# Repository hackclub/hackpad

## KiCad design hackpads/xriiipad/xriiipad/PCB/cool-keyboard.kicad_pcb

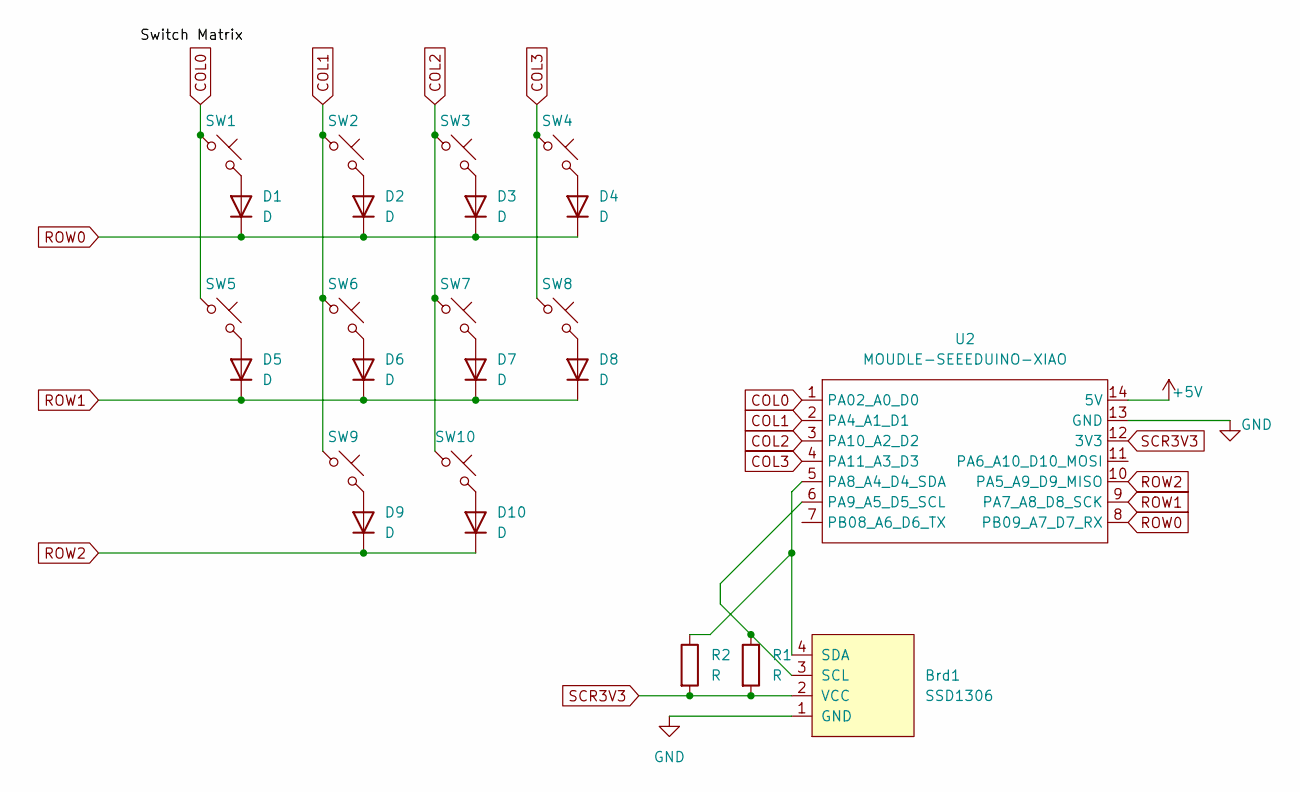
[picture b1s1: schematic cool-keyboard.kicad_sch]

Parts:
Brd1: SSD1306; 128x64OLED
D1, D2, D3, D4, D5, D6, D7, D8, D9, D10: D; D_A-405_P10.16mm_Horizontal
R1, R2: R; R_Axial_DIN0204_L3.6mm_D1.6mm_P5.08mm_Horizontal
SW1, SW2, SW3, SW4, SW5, SW6, SW7, SW8, SW9, SW10: SW_Push_45deg; MX-Solderable-1U
U2: MOUDLE-SEEEDUINO-XIAO; MOUDLE14P-2.54-21X17.8MM

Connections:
+5V: U2.14 (5V)
COL0: SW1.1, SW5.1, U2.1 (PA02_A0_D0)
COL1: SW2.1, SW6.1, SW9.1, U2.2 (PA4_A1_D1)
COL2: SW3.1, SW7.1, SW10.1, U2.3 (PA10_A2_D2)
COL3: SW4.1, SW8.1, U2.4 (PA11_A3_D3)
GND: Brd1.1 (GND), U2.13 (GND)
unnamed: Brd1.3 (SCL), R1.1, U2.6 (PA9_A5_D5_SCL)
unnamed: Brd1.4 (SDA), R2.1, U2.5 (PA8_A4_D4_SDA)
unnamed: D1.2 (A), SW1.2
unnamed: D2.2 (A), SW2.2
unnamed: D3.2 (A), SW3.2
unnamed: D4.2 (A), SW4.2
unnamed: D5.2 (A), SW5.2
unnamed: D6.2 (A), SW6.2
unnamed: D7.2 (A), SW7.2
unnamed: D8.2 (A), SW8.2
unnamed: D9.2 (A), SW9.2
unnamed: D10.2 (A), SW10.2
ROW0: D1.1 (K), D2.1 (K), D3.1 (K), D4.1 (K), U2.8 (PB09_A7_D7_RX)
ROW1: D5.1 (K), D6.1 (K), D7.1 (K), D8.1 (K), U2.9 (PA7_A8_D8_SCK)
ROW2: D9.1 (K), D10.1 (K), U2.10 (PA5_A9_D9_MISO)
SCR3V3: Brd1.2 (VCC), R1.2, R2.2, U2.12 (3V3)

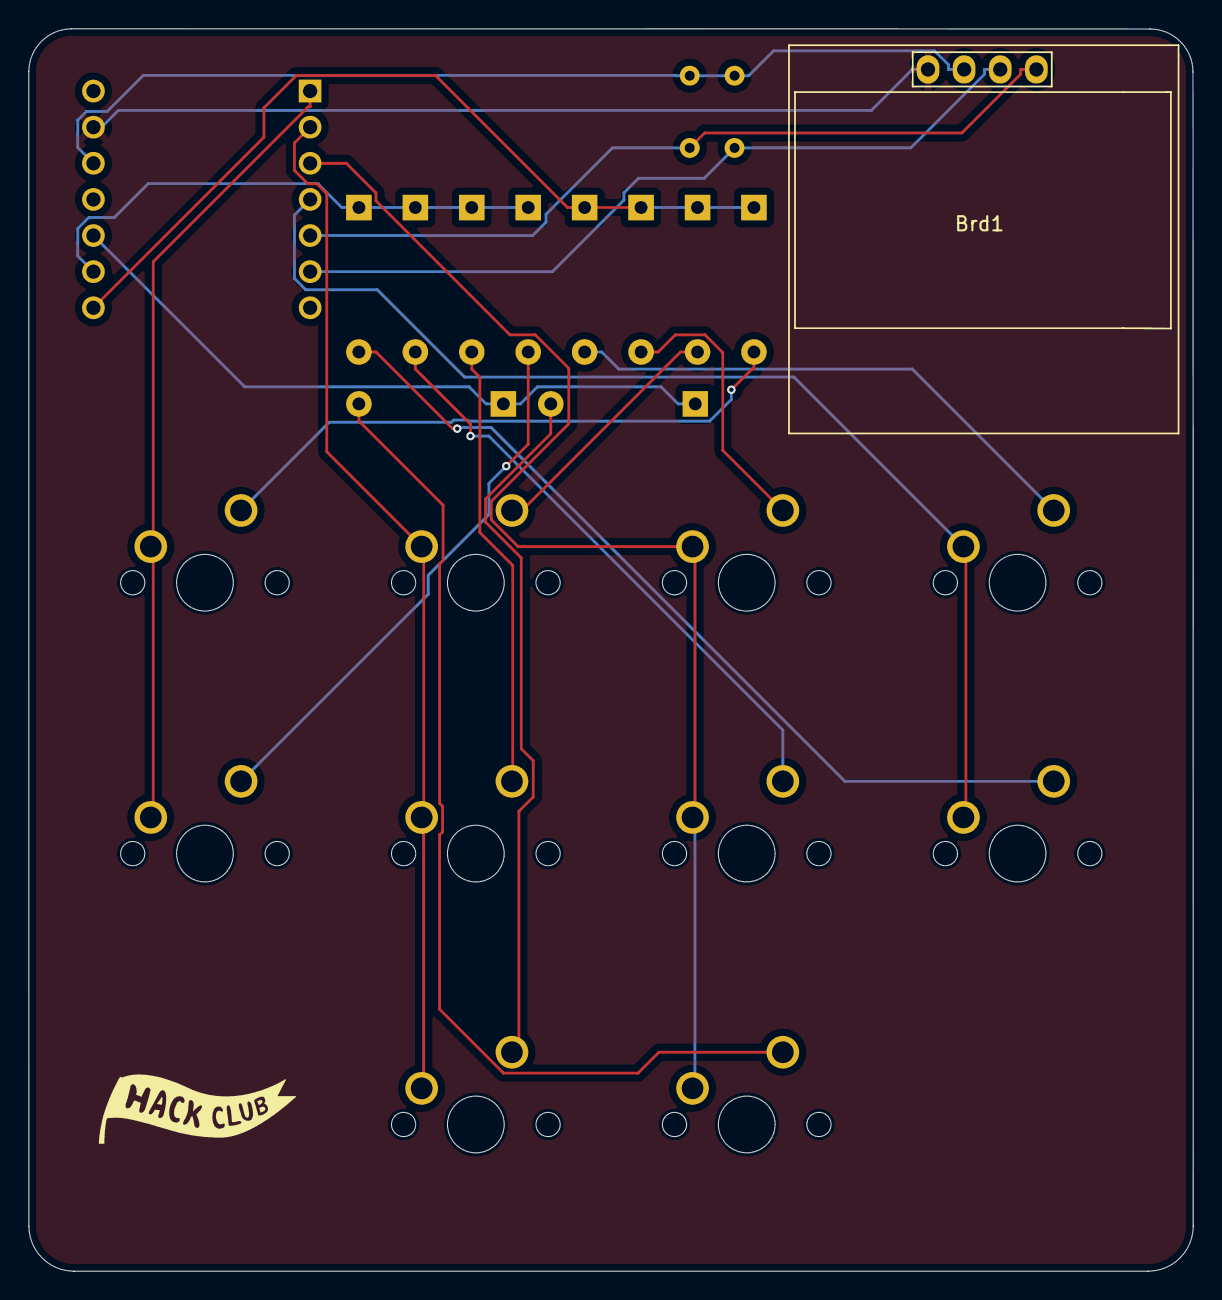
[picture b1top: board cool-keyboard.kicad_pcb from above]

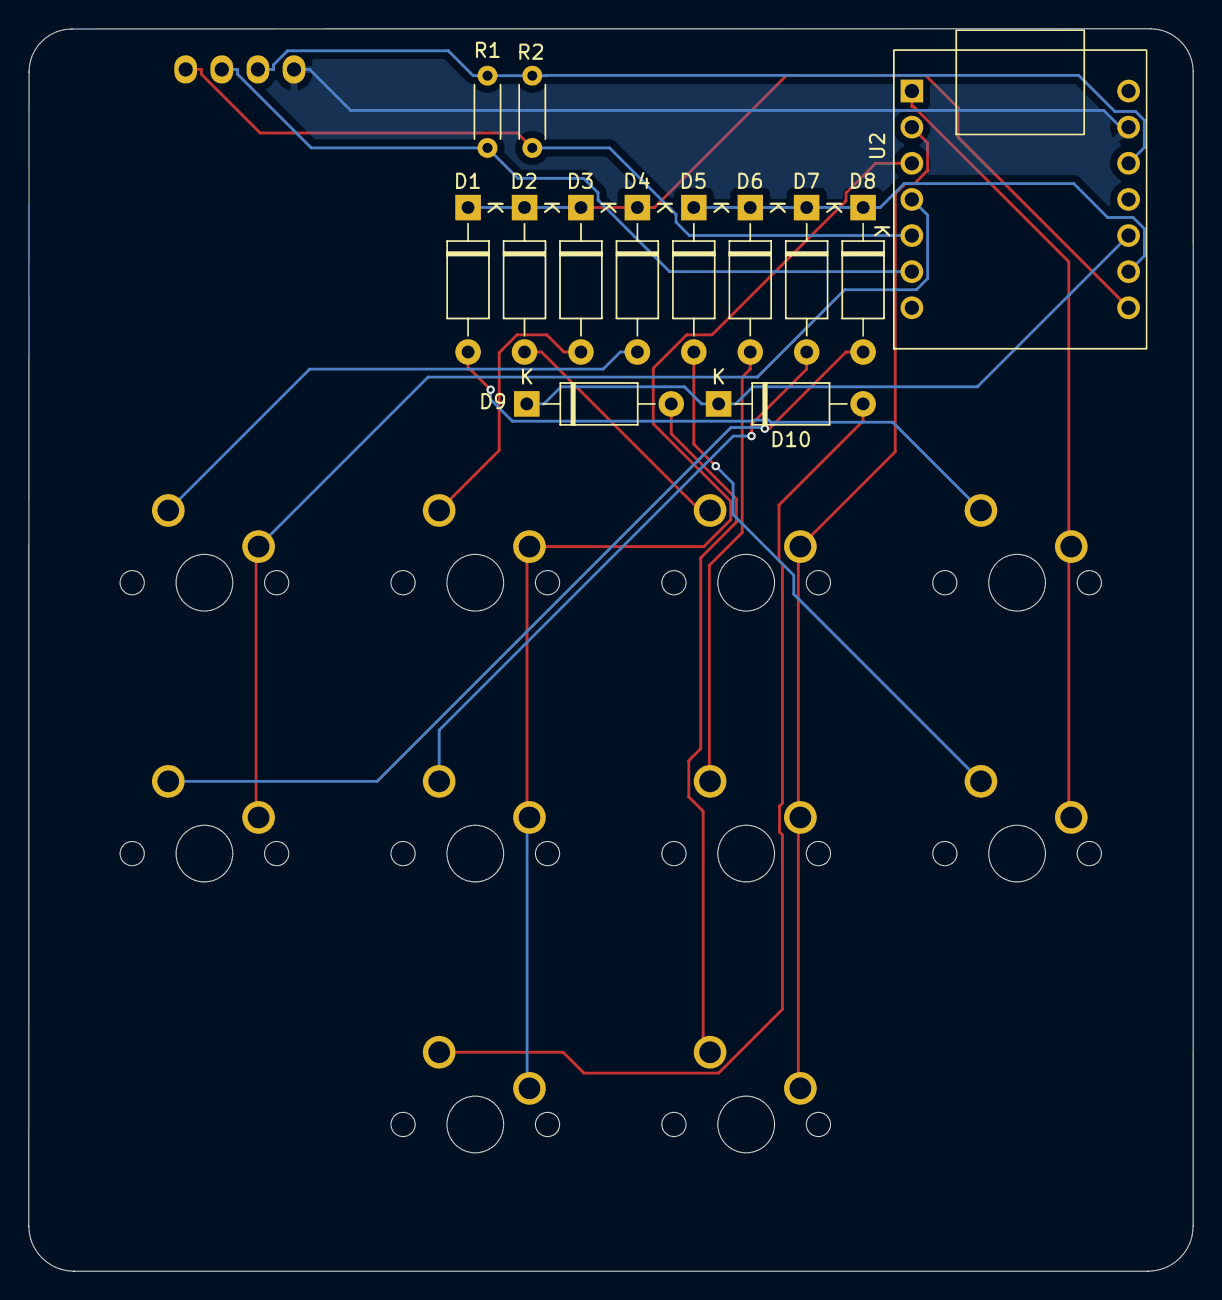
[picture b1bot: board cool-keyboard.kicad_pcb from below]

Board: 2 copper layers, 81.9 x 87.4 mm, 24 parts (13 on the bottom side), 21 nets.

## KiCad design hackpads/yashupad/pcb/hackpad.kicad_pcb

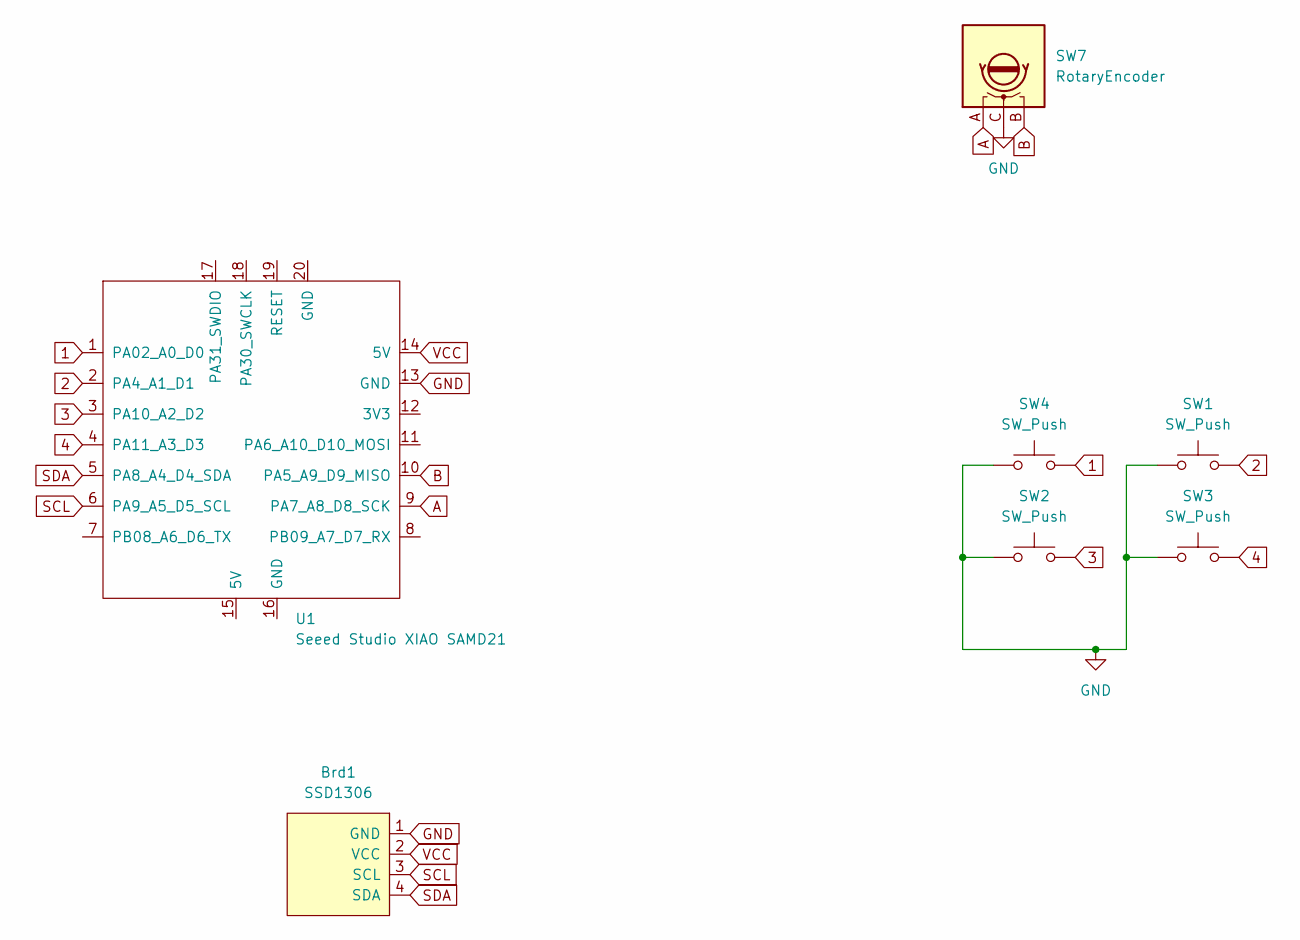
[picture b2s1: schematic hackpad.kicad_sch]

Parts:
Brd1: SSD1306; 128x64OLED
SW1, SW2, SW3, SW4: SW_Push; SW_Cherry_MX_1.00u_PCB
SW7: RotaryEncoder; RotaryEncoder_Alps_EC11E-Switch_Vertical_H20mm
U1: Seeed Studio XIAO SAMD21; XIAO-Generic-Thruhole-14P-2.54-21X17.8MM

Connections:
1: SW4.2, U1.1 (PA02_A0_D0)
2: SW1.2, U1.2 (PA4_A1_D1)
3: SW2.2, U1.3 (PA10_A2_D2)
4: SW3.2, U1.4 (PA11_A3_D3)
A: SW7.A, U1.9 (PA7_A8_D8_SCK)
B: SW7.B, U1.10 (PA5_A9_D9_MISO)
GND: Brd1.1 (GND), SW1.1, SW2.1, SW3.1, SW4.1, SW7.C, U1.13 (GND)
SCL: Brd1.3 (SCL), U1.6 (PA9_A5_D5_SCL)
SDA: Brd1.4 (SDA), U1.5 (PA8_A4_D4_SDA)
VCC: Brd1.2 (VCC), U1.14 (5V)

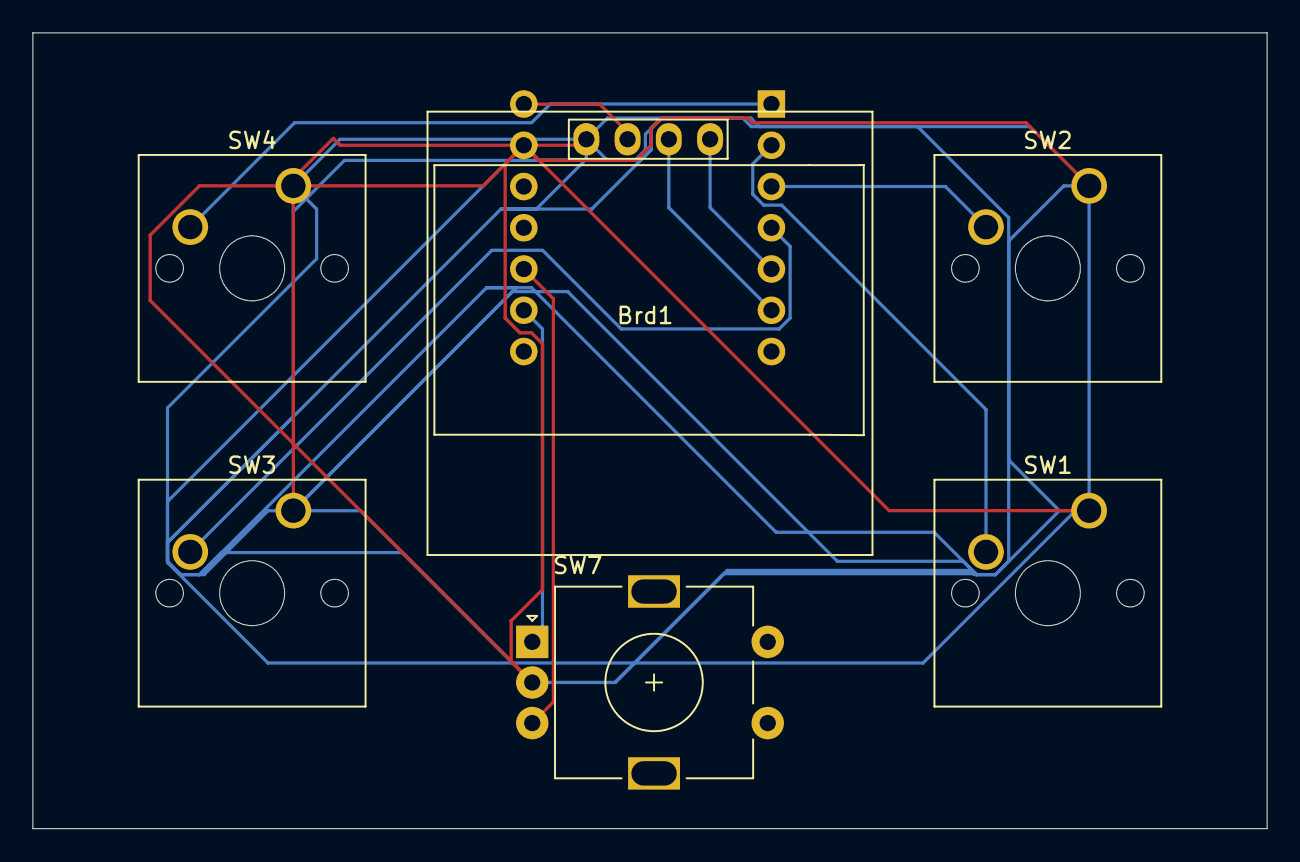
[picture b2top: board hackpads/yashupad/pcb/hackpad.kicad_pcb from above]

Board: 2 copper layers, 76.0 x 49.0 mm, 7 parts (1 on the bottom side), 10 nets.

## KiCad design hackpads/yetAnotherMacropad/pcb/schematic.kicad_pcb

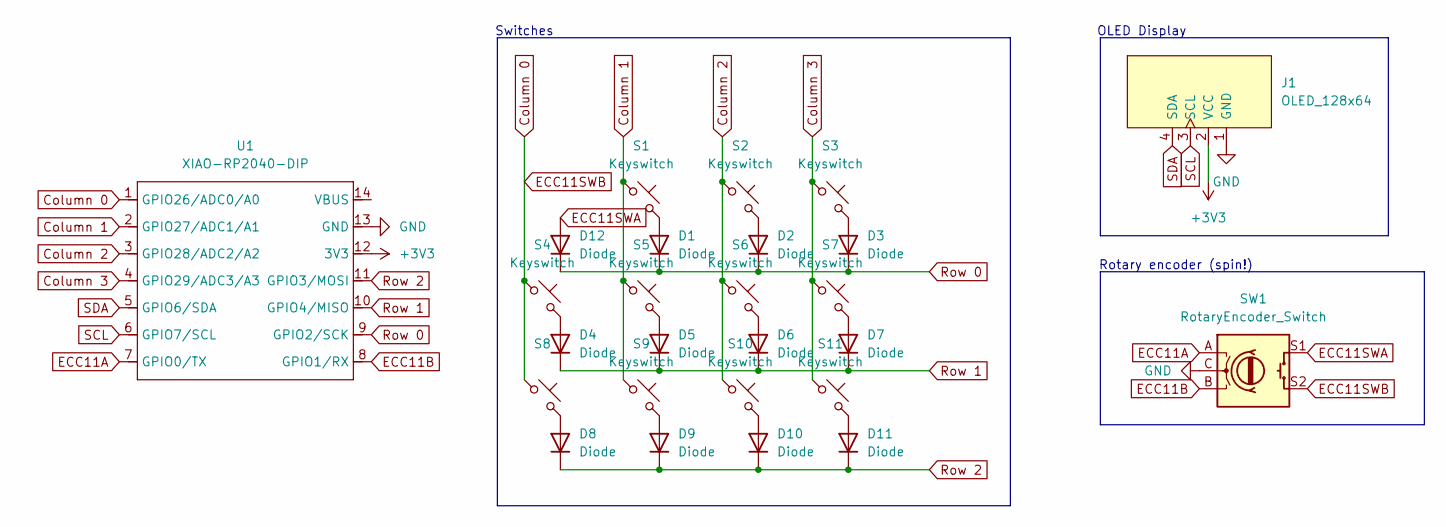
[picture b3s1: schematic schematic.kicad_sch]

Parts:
D1, D2, D3, D4, D5, D6, D7, D8, D9, D10, D11, D12: Diode; Diode_DO-35
J1: OLED_128x64; MODULE_DM-OLED096-636
S1, S2, S3, S4, S5, S6, S7, S8, S9, S10, S11: Keyswitch; MX_PCB_1.00u
SW1: RotaryEncoder_Switch; RotaryEncoder_Alps_EC11E-Switch_Vertical_H20mm
U1: XIAO-RP2040-DIP; MOUDLE14P-2.54-21X17.8MM

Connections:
+3V3: J1.2 (VCC), U1.12 (3V3)
Column 0: S4.1, S8.1, SW1.S2, U1.1 (GPIO26/ADC0/A0)
Column 1: S1.1, S5.1, S9.1, U1.2 (GPIO27/ADC1/A1)
Column 2: S2.1, S6.1, S10.1, U1.3 (GPIO28/ADC2/A2)
Column 3: S3.1, S7.1, S11.1, U1.4 (GPIO29/ADC3/A3)
ECC11A: SW1.A, U1.7 (GPIO0/TX)
ECC11B: SW1.B, U1.8 (GPIO1/RX)
ECC11SWA: D12.2 (A), SW1.S1
GND: J1.1 (GND), SW1.C, U1.13 (GND)
unnamed: D1.2 (A), S1.2
unnamed: D2.2 (A), S2.2
unnamed: D3.2 (A), S3.2
unnamed: D4.2 (A), S4.2
unnamed: D5.2 (A), S5.2
unnamed: D6.2 (A), S6.2
unnamed: D7.2 (A), S7.2
unnamed: D8.2 (A), S8.2
unnamed: D9.2 (A), S9.2
unnamed: D10.2 (A), S10.2
unnamed: D11.2 (A), S11.2
Row 0: D1.1 (K), D2.1 (K), D3.1 (K), D12.1 (K), U1.9 (GPIO2/SCK)
Row 1: D4.1 (K), D5.1 (K), D6.1 (K), D7.1 (K), U1.10 (GPIO4/MISO)
Row 2: D8.1 (K), D9.1 (K), D10.1 (K), D11.1 (K), U1.11 (GPIO3/MOSI)
SCL: J1.3 (SCL), U1.6 (GPIO7/SCL)
SDA: J1.4 (SDA), U1.5 (GPIO6/SDA)

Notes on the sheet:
Switches
Rotary encoder (spin!)
OLED Display

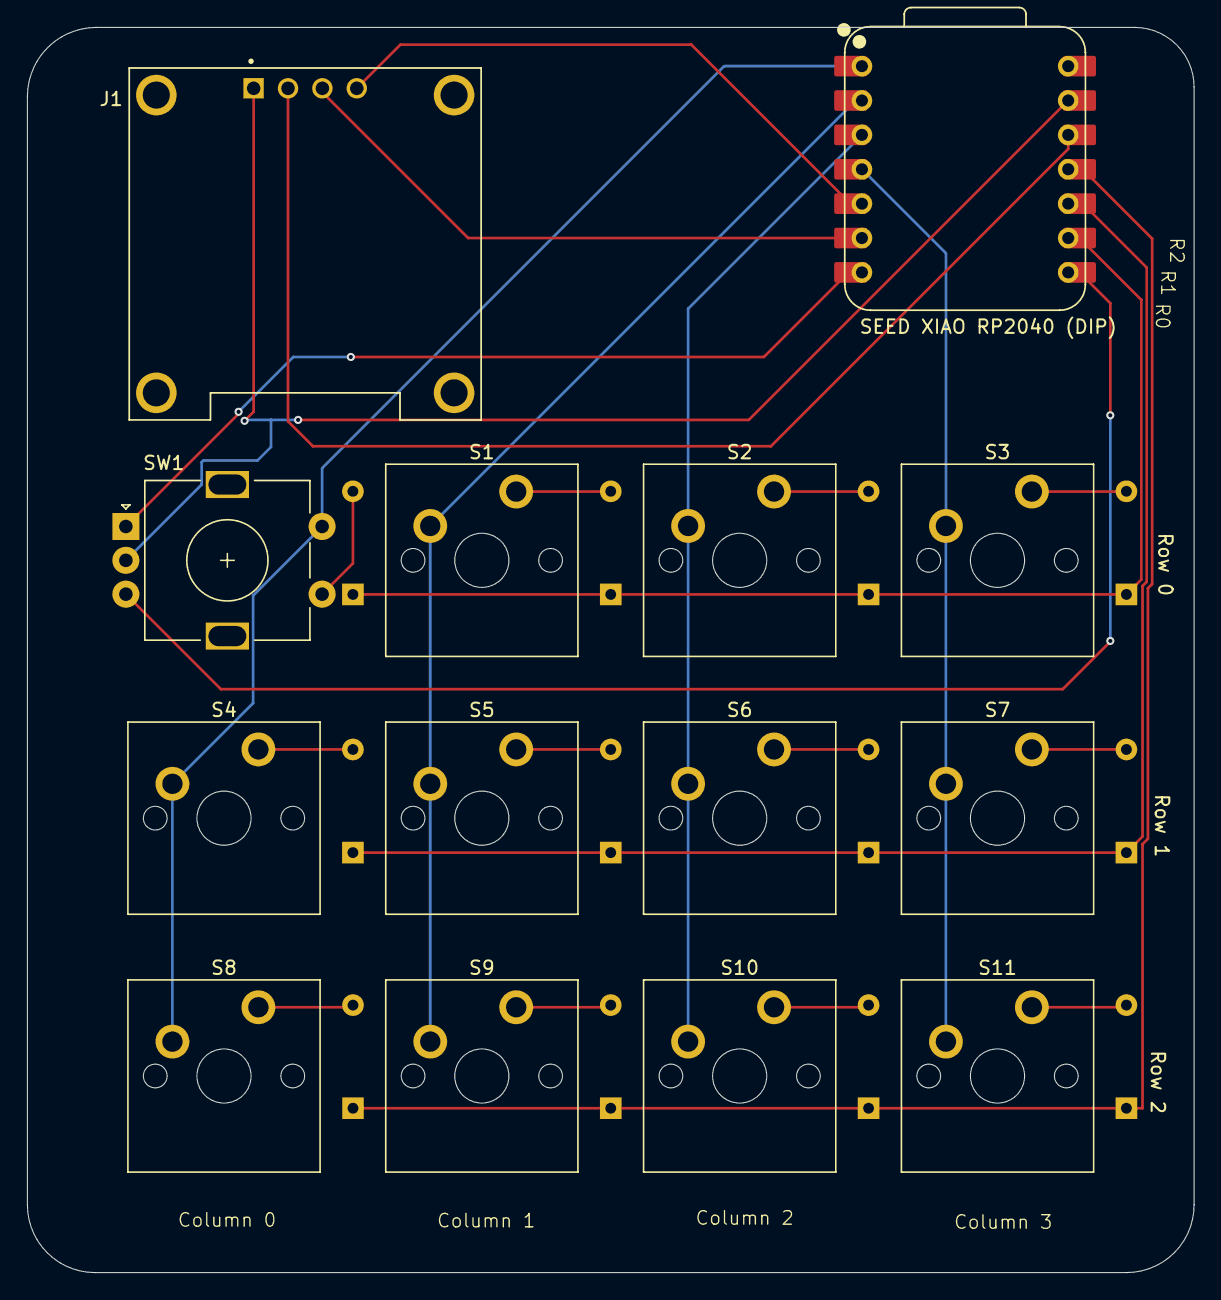
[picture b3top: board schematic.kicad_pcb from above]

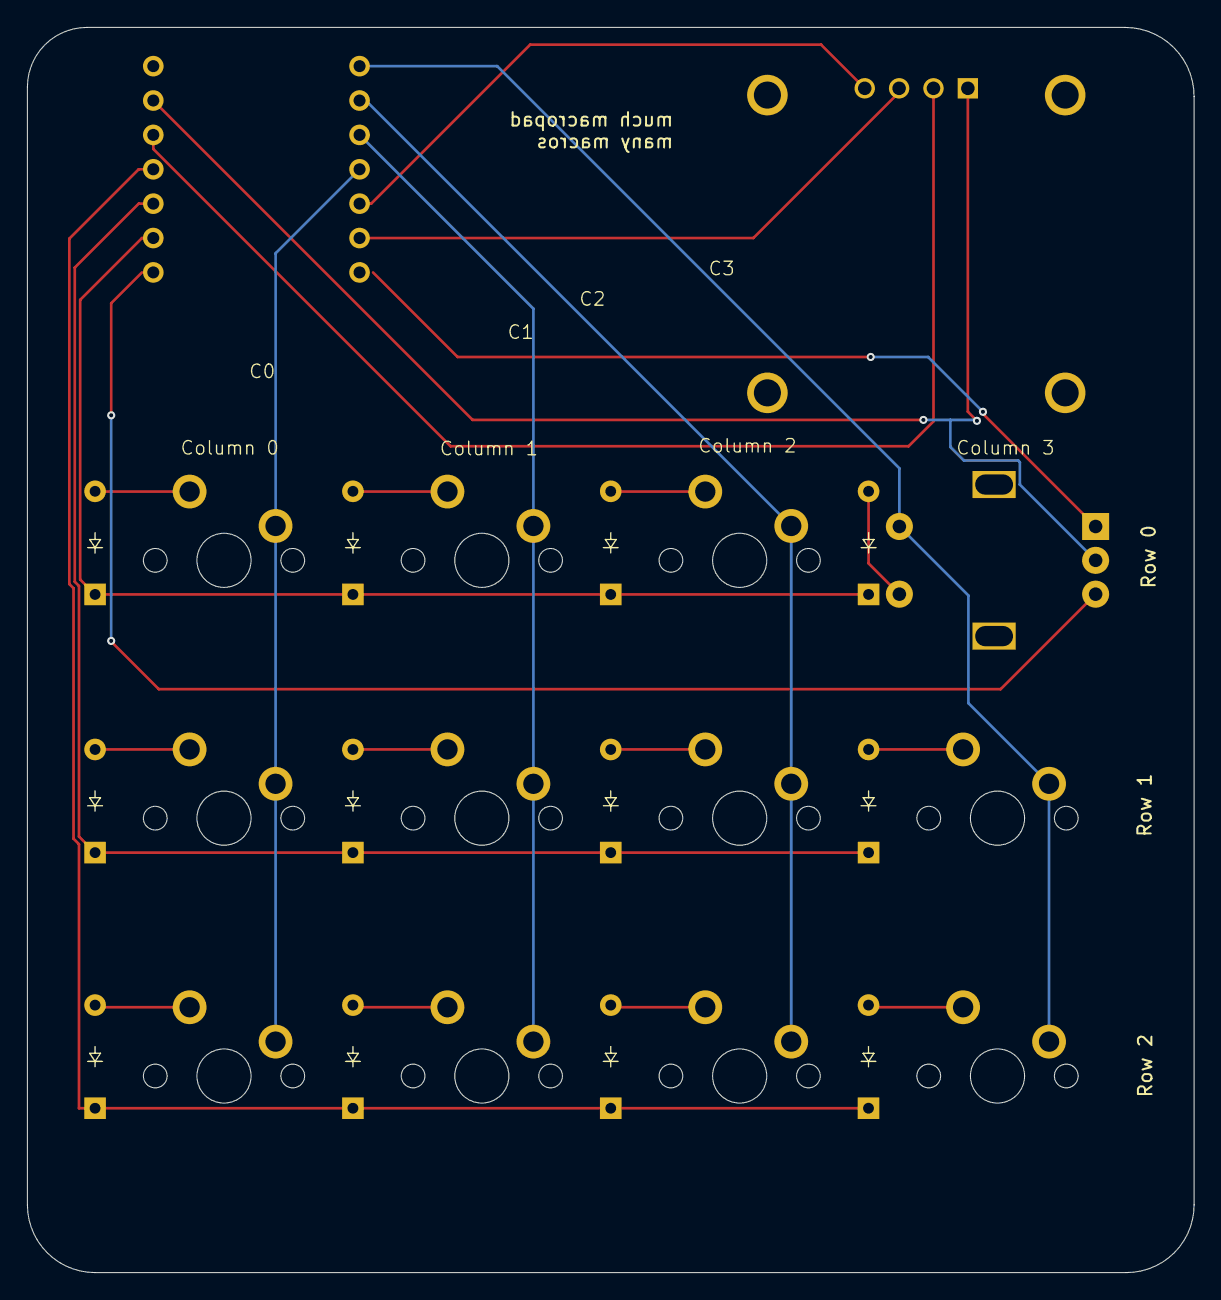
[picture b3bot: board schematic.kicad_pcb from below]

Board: 2 copper layers, 86.2 x 92.0 mm, 26 parts (12 on the bottom side), 25 nets.

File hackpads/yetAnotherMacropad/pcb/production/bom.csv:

Designator,Footprint,Quantity,Value,LCSC Part #
"D1, D10, D11, D12, D2, D3, D4, D5, D6, D7, D8, D9",Diode_DO-35,12,Diode,
J1,MODULE_DM-OLED096-636,1,OLED_128x64,
"S1, S10, S11, S2, S3, S4, S5, S6, S7, S8, S9",MX_PCB_1.00u,11,Keyswitch,
SW1,RotaryEncoder_Alps_EC11E-Switch_Vertical_H20mm,1,RotaryEncoder_Switch,
U1,XIAO-RP2040-DIP,1,XIAO-RP2040-DIP,

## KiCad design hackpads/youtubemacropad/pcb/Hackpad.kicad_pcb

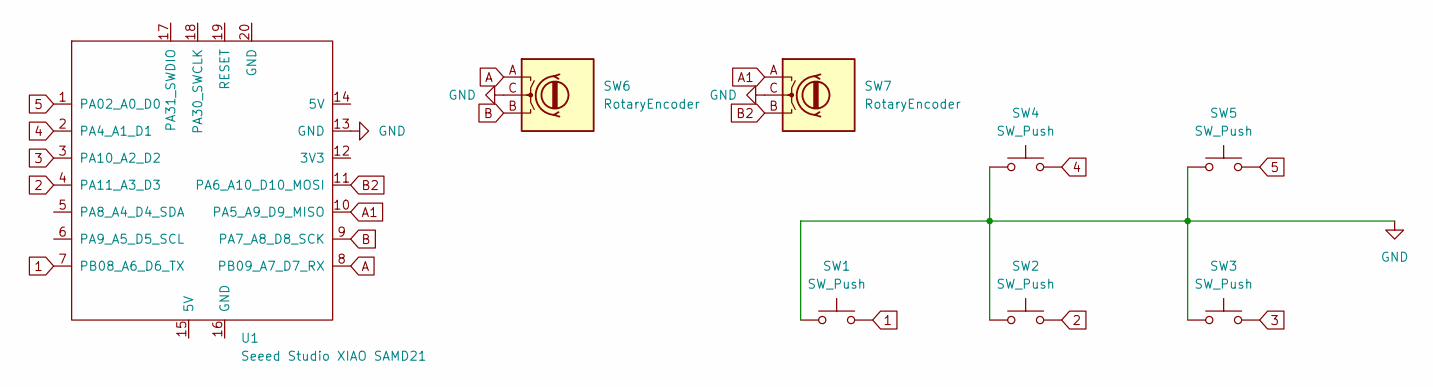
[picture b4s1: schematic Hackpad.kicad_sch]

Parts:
SW1, SW2, SW3, SW4, SW5: SW_Push; SW_Cherry_MX_1.00u_PCB
SW6, SW7: RotaryEncoder; RotaryEncoder_Alps_EC11E-Switch_Vertical_H20mm
U1: Seeed Studio XIAO SAMD21; XIAO-Generic-Thruhole-14P-2.54-21X17.8MM

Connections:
1: SW1.2, U1.7 (PB08_A6_D6_TX)
2: SW2.2, U1.4 (PA11_A3_D3)
3: SW3.2, U1.3 (PA10_A2_D2)
4: SW4.2, U1.2 (PA4_A1_D1)
5: SW5.2, U1.1 (PA02_A0_D0)
A: SW6.A, U1.8 (PB09_A7_D7_RX)
A1: SW7.A, U1.10 (PA5_A9_D9_MISO)
B: SW6.B, U1.9 (PA7_A8_D8_SCK)
B2: SW7.B, U1.11 (PA6_A10_D10_MOSI)
GND: SW1.1, SW2.1, SW3.1, SW4.1, SW5.1, SW6.C, SW7.C, U1.13 (GND)

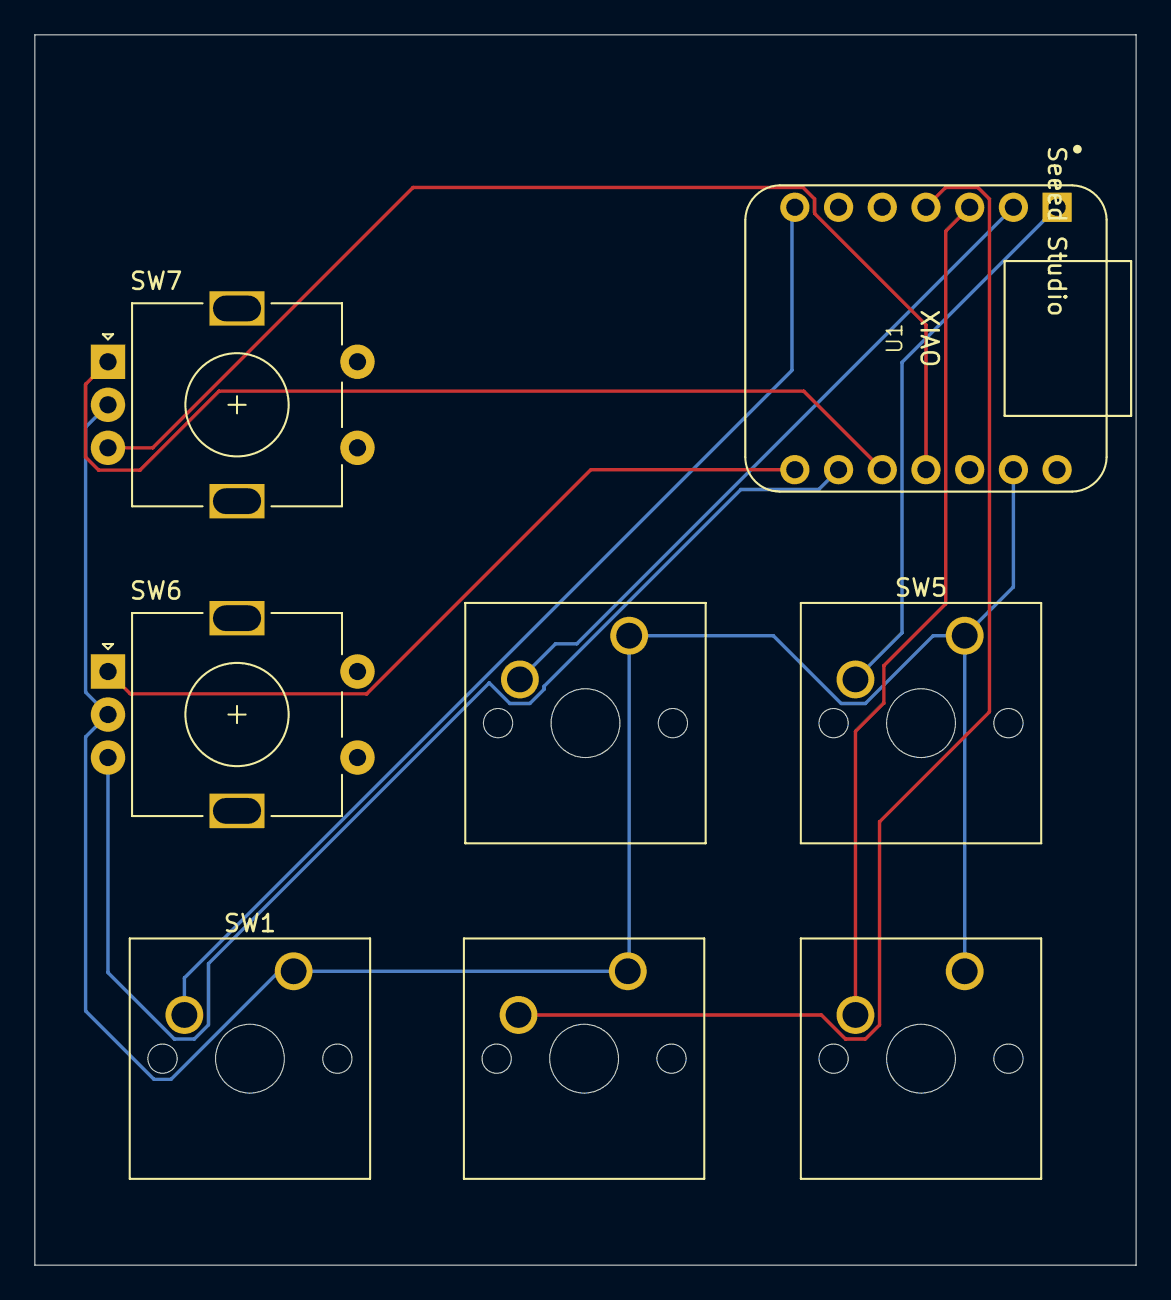
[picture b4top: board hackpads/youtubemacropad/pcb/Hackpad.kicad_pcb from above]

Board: 2 copper layers, 64.0 x 71.5 mm, 8 parts (0 on the bottom side), 10 nets.

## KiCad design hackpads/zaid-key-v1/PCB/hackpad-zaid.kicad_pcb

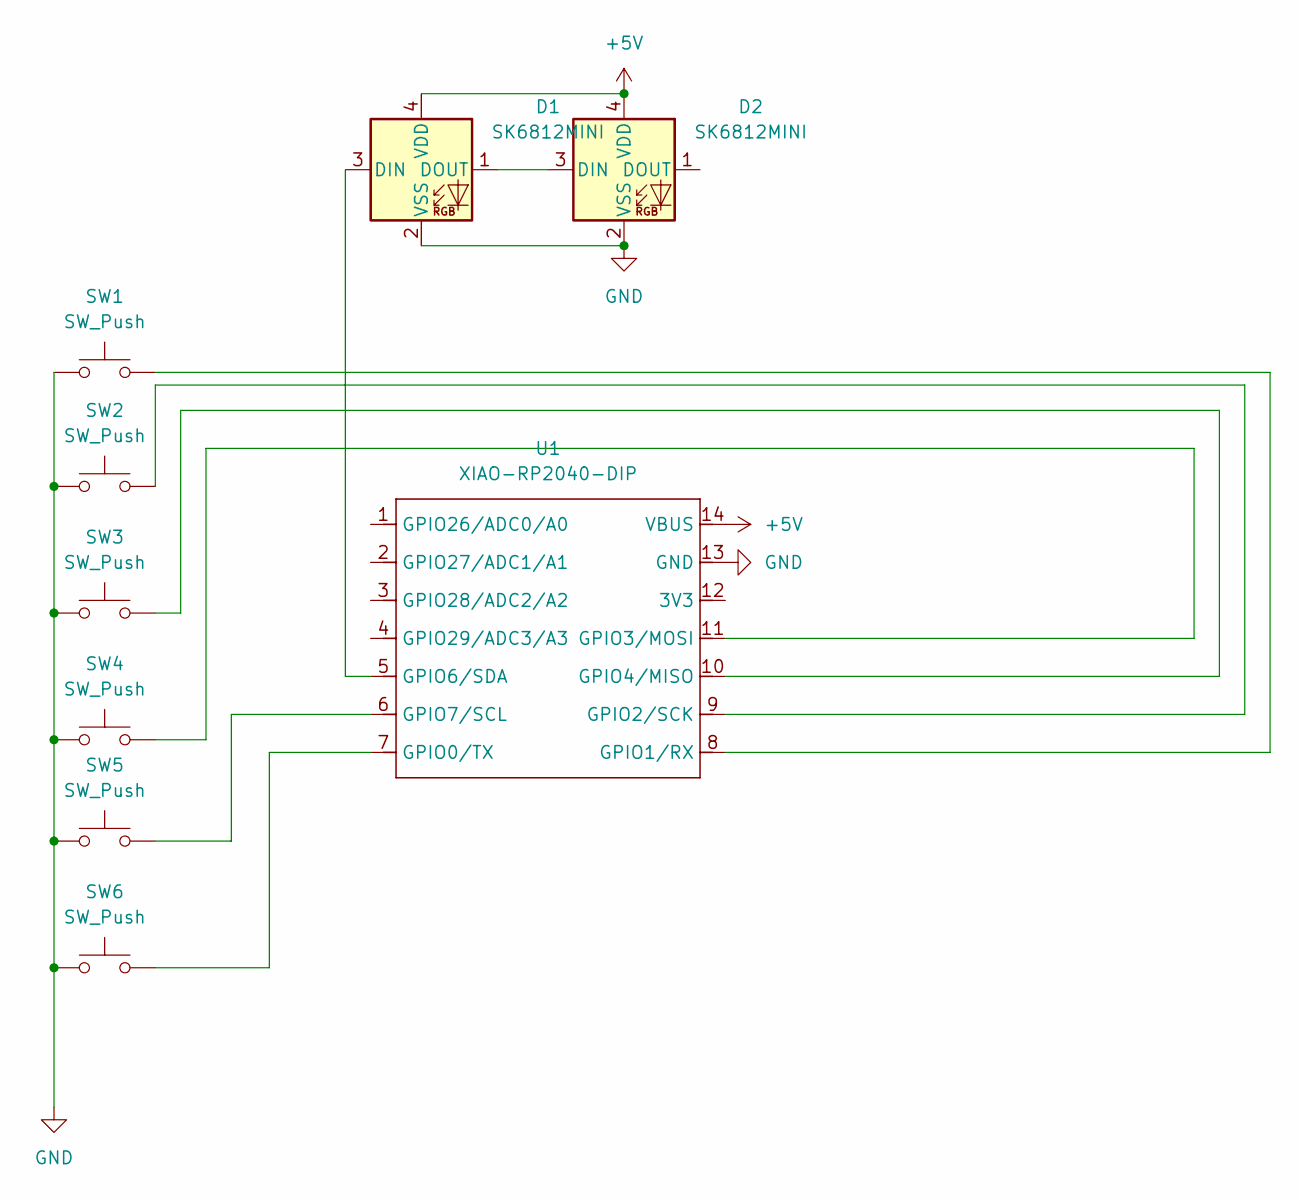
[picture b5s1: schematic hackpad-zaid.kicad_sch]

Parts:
D1, D2: SK6812MINI; LED_SK6812MINI_PLCC4_3.5x3.5mm_P1.75mm
SW1, SW2, SW3, SW4, SW5, SW6: SW_Push; SW_Cherry_MX_1.00u_PCB
U1: XIAO-RP2040-DIP

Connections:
+5V: D1.4 (VDD), D2.4 (VDD), U1.14 (VBUS)
GND: D1.2 (VSS), D2.2 (VSS), SW1.2, SW2.1, SW3.1, SW4.1, SW5.1, SW6.1, U1.13 (GND)
unnamed: D1.3 (DIN), U1.5 (GPIO6/SDA)
unnamed: D1.1 (DOUT), D2.3 (DIN)
unnamed: SW6.2, U1.7 (GPIO0/TX)
unnamed: SW1.1, U1.8 (GPIO1/RX)
unnamed: SW2.2, U1.9 (GPIO2/SCK)
unnamed: SW4.2, U1.11 (GPIO3/MOSI)
unnamed: SW3.2, U1.10 (GPIO4/MISO)
unnamed: SW5.2, U1.6 (GPIO7/SCL)

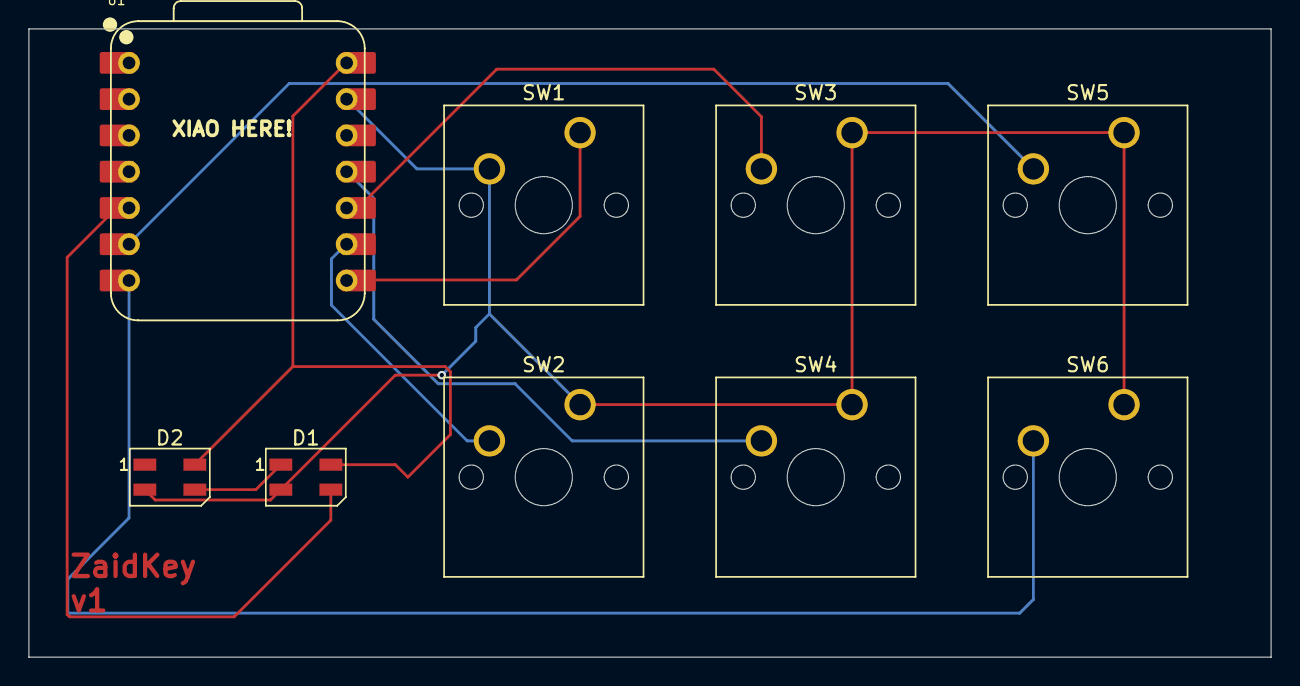
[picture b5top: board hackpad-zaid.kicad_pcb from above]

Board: 2 copper layers, 87.0 x 44.0 mm, 9 parts (0 on the bottom side), 10 nets.

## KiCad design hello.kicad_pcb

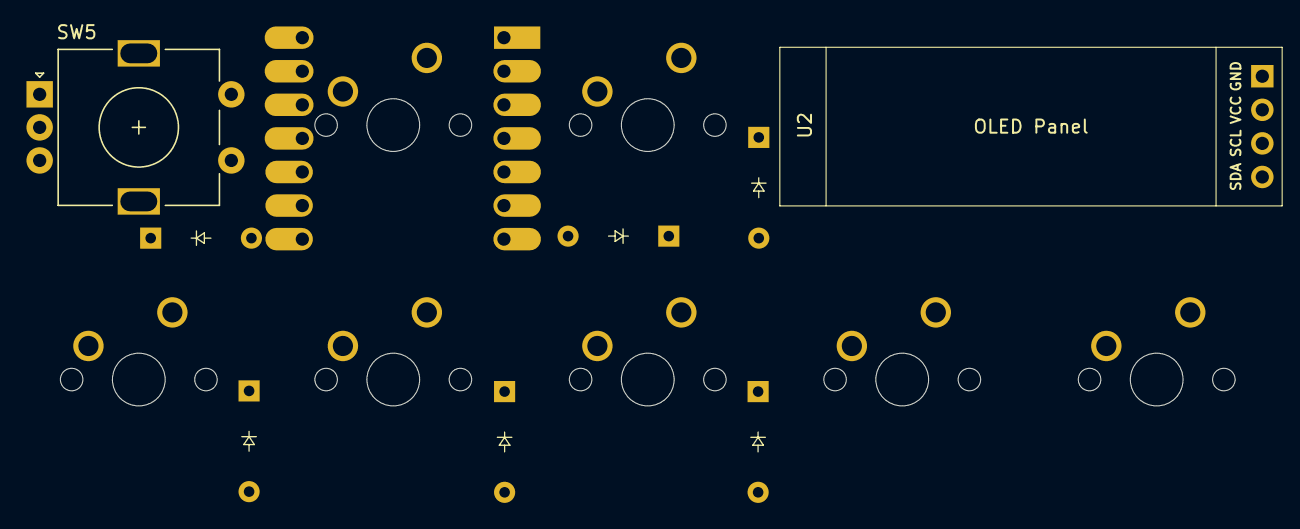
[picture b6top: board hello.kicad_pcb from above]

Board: 2 copper layers, 16 parts (1 on the bottom side), 18 nets, no tracks yet.

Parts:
D1, D2, D5, D6, D7, D8: D; Diode_DO-35
D9: D; 1U-Switch
SW1, SW2, SW3, SW4, SW6, SW7: SW_Push_45deg; 1U-Switch
SW5: RotaryEncoder_Switch; RotaryEncoder_Alps_EC11E-Switch_Vertical_H20mm
U1: MOUDLE-SEEEDUINO-XIAO; XIAO
U2: DM-OLED096-636; SSD1306-0.91-OLED-4pin-128x32

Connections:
Col 1: D2.1 (K), D5.1 (K), D7.1 (K), SW1.1, SW5.S1, U1.1 (PA02_A0_D0), U1.5 (PA8_A4_D4_SDA)
Col 2: SW2.1, SW3.1, U1.2 (PA4_A1_D1)
Col 3: SW4.1, SW6.1, U1.3 (PA10_A2_D2)
Col 4: SW7.1, U1.4 (PA11_A3_D3)
Encoder A: SW5.A, U1.7 (PB08_A6_D6_TX)
Encoder B: SW5.B, U1.8 (PB09_A7_D7_RX)
Encoder S2: D2.2 (A), SW5.S2
GND: SW5.C, U1.13 (GND), U2.1 (GND)
unnamed: D1.2 (A), SW1.2
unnamed: D5.2 (A), SW2.2
unnamed: D6.2 (A), SW3.2
unnamed: D7.2 (A), SW4.2
unnamed: D8.2 (A), SW6.2
unnamed: D9.2 (A), SW7.2
OLED SCL: U1.10 (PA5_A9_D9_MISO), U2.3 (SCL)
OLED SDA: U1.9 (PA7_A8_D8_SCK), U2.4 (SDA)
Row 2: D1.1 (K), D6.1 (K), D8.1 (K), D9.1 (K), U1.6 (PA9_A5_D5_SCL)
VCC: U1.14 (5V), U2.2 (VCC_IN)
